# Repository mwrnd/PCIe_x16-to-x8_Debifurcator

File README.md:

# PCIe x16-to-x8 Debifurcator

Designed for use with the [Alveo U25](https://www.xilinx.com/products/boards-and-kits/alveo/u25.html) which has an x16 PCIe interface that is bifurcated to two x8 interfaces, one for the [SFC9250 X2 GbE Controller](https://www.xilinx.com/products/boards-and-kits/x2-series.html) and the other for the [XCZU19EG FPGA](https://www.xilinx.com/products/silicon-devices/soc/zynq-ultrascale-mpsoc.html#eg). This board connects the FPGA's PCIe x8 interface directly to a host system. The X2 GbE Controller is disconnected and ignored.

Only a straddle-mount PCIe x16 Connector is required, such as: [10025026-10103TLF](https://www.trustedparts.com/en/search/10025026-10103TLF), [10025026-10003TLF](https://www.trustedparts.com/en/search/10025026-10003TLF), or [10146027-A40010LF](https://www.trustedparts.com/en/search/10146027-A40010LF).

Related Projects: [alveo_u25_notes](https://github.com/mwrnd/alveo_u25_notes), [AlveoU25_JTAG_Adapter](https://github.com/mwrnd/AlveoU25_JTAG_Adapter), [ATX_Boot_Delay](https://github.com/mwrnd/ATX_Boot_Delay)

# Testing and Use Example

I have been able to [successfully test an XDMA design](https://github.com/mwrnd/alveo_u25_notes) using the debifurcator and an Alveo U25 in a system that does not support PCIe Bifurcation.

The XCZU19EG uses its ARM processor to configure the FPGA's Programmable Logic (PL) bitstream. It is difficult to get this to finish within the [PCIe Specification's 100ms time limit](https://pcisig.com/specifications/ecr_ecn_process?speclib=100+ms). Motherboard boot must be delayed to allow the FPGA to configure itself before PCIe devices are enumerated by the host system. This can be accomplished by toggling the POWER button, then pressing and holding the RESET button for a second before releasing it. Or, [connect a capacitor across the reset pins of an ATX motherboard's Front Panel Header](https://github.com/mwrnd/ATX_Boot_Delay):

# PCB Layout

All differential pairs are length-matched to within 1mm both inter-pair and intra-pair.

# Schematic

# Assembly

The PCIe Connector's Mounting Post needs to be snapped off with needle-nose pliers.

# PCB Layer Stackup

4-Layer PCB stackup taken from [JLCPCB](https://jlcpcb.com/capabilities/pcb-capabilities).

Differential Impedance parameters were calculated using the [DigiKey Online Calculator](https://www.digikey.com/en/resources/conversion-calculators/conversion-calculator-pcb-trace-impedance).

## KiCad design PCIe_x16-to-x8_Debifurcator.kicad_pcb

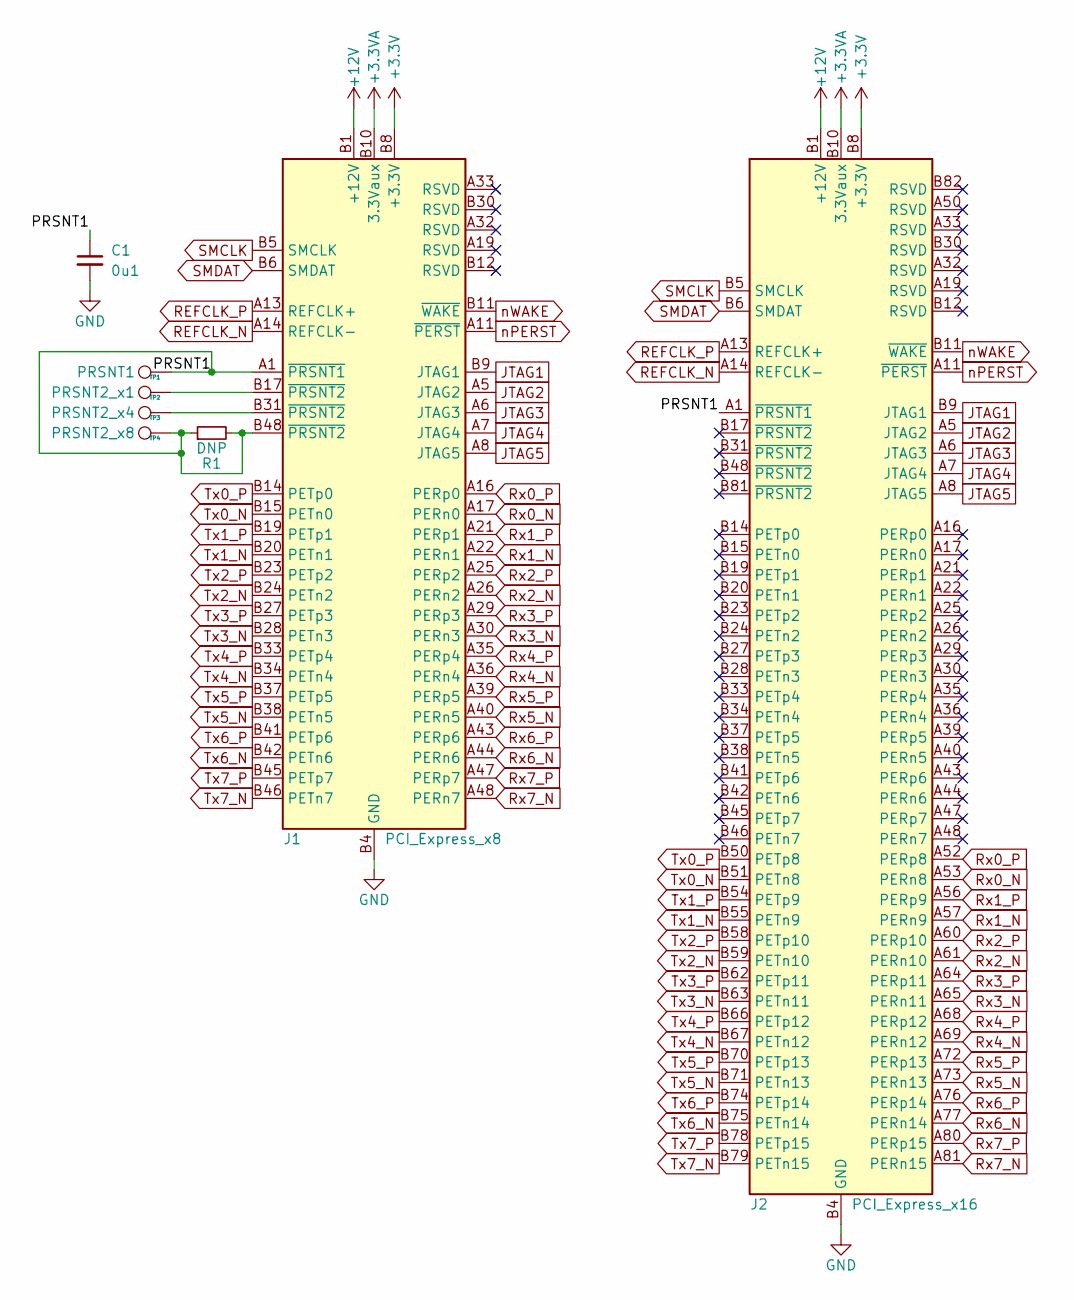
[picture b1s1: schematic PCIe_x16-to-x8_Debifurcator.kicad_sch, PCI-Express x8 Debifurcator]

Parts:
C1: 0u1; C_0603_1608Metric_Pad1.08x0.95mm_HandSolder
J1: PCI_Express_x8; BUS_PCIexpress_x8
J2: PCI_Express_x16; BUS_PCIexpress_x16
R1: DNP; R_0603_1608Metric
TP1: PRSNT1; PinHeader_1x01_P1.00mm_Vertical
TP2: PRSNT2_x1; PinHeader_1x01_P1.00mm_Vertical
TP3: PRSNT2_x4; PinHeader_1x01_P1.00mm_Vertical
TP4: PRSNT2_x8; PinHeader_1x01_P1.00mm_Vertical

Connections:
+3.3V: J1.A9 (+3.3V), J1.A10 (+3.3V), J1.B8 (+3.3V), J2.A9 (+3.3V), J2.A10 (+3.3V), J2.B8 (+3.3V)
+3.3VA: J1.B10 (3.3Vaux), J2.B10 (3.3Vaux)
+12V: J1.A2 (+12V), J1.A3 (+12V), J1.B1 (+12V), J1.B2 (+12V), J1.B3 (+12V), J2.A2 (+12V), J2.A3 (+12V), J2.B1 (+12V), J2.B2 (+12V), J2.B3 (+12V)
/PRSNT1: C1.1, J1.A1 (~PRSNT1), J1.B48 (~PRSNT2), J2.A1 (~PRSNT1), R1.1, R1.2, TP1.1, TP4.1
GND: C1.2, J1.A4 (GND), J1.A12 (GND), J1.A15 (GND), J1.A18 (GND), J1.A20 (GND), J1.A23 (GND), J1.A24 (GND), J1.A27 (GND), J1.A28 (GND), J1.A31 (GND), J1.A34 (GND), J1.A37 (GND), J1.A38 (GND), J1.A41 (GND), J1.A42 (GND), J1.A45 (GND), J1.A46 (GND), J1.A49 (GND), J1.B4 (GND), J1.B7 (GND), J1.B13 (GND), J1.B16 (GND), J1.B18 (GND), J1.B21 (GND), J1.B22 (GND), J1.B25 (GND), J1.B26 (GND), J1.B29 (GND), J1.B32 (GND), J1.B35 (GND), J1.B36 (GND), J1.B39 (GND), J1.B40 (GND), J1.B43 (GND), J1.B44 (GND), J1.B47 (GND), J1.B49 (GND), J2.A4 (GND), J2.A12 (GND), J2.A15 (GND), J2.A18 (GND), J2.A20 (GND), J2.A23 (GND), J2.A24 (GND), J2.A27 (GND), J2.A28 (GND), J2.A31 (GND), J2.A34 (GND), J2.A37 (GND), J2.A38 (GND), J2.A41 (GND), J2.A42 (GND), J2.A45 (GND), J2.A46 (GND), J2.A49 (GND), J2.A51 (GND), J2.A54 (GND), J2.A55 (GND), J2.A58 (GND), J2.A59 (GND), J2.A62 (GND), J2.A63 (GND), J2.A66 (GND), J2.A67 (GND), J2.A70 (GND), J2.A71 (GND), J2.A74 (GND), J2.A75 (GND), J2.A78 (GND), J2.A79 (GND), J2.A82 (GND), J2.B4 (GND), J2.B7 (GND), J2.B13 (GND), J2.B16 (GND), J2.B18 (GND), J2.B21 (GND), J2.B22 (GND), J2.B25 (GND), J2.B26 (GND), J2.B29 (GND), J2.B32 (GND), J2.B35 (GND), J2.B36 (GND), J2.B39 (GND), J2.B40 (GND), J2.B43 (GND), J2.B44 (GND), J2.B47 (GND), J2.B49 (GND), J2.B52 (GND), J2.B53 (GND), J2.B56 (GND), J2.B57 (GND), J2.B60 (GND), J2.B61 (GND), J2.B64 (GND), J2.B65 (GND), J2.B68 (GND), J2.B69 (GND), J2.B72 (GND), J2.B73 (GND), J2.B76 (GND), J2.B77 (GND), J2.B80 (GND)
JTAG1: J1.B9 (JTAG1), J2.B9 (JTAG1)
JTAG2: J1.A5 (JTAG2), J2.A5 (JTAG2)
JTAG3: J1.A6 (JTAG3), J2.A6 (JTAG3)
JTAG4: J1.A7 (JTAG4), J2.A7 (JTAG4)
JTAG5: J1.A8 (JTAG5), J2.A8 (JTAG5)
unnamed: J1.B17 (~PRSNT2), TP2.1
unnamed: J1.B31 (~PRSNT2), TP3.1
REFCLK_N: J1.A14 (REFCLK-), J2.A14 (REFCLK-)
REFCLK_P: J1.A13 (REFCLK+), J2.A13 (REFCLK+)
Rx0_N: J1.A17 (PERn0), J2.A53 (PERn8)
Rx0_P: J1.A16 (PERp0), J2.A52 (PERp8)
Rx1_N: J1.A22 (PERn1), J2.A57 (PERn9)
Rx1_P: J1.A21 (PERp1), J2.A56 (PERp9)
Rx2_N: J1.A26 (PERn2), J2.A61 (PERn10)
Rx2_P: J1.A25 (PERp2), J2.A60 (PERp10)
Rx3_N: J1.A30 (PERn3), J2.A65 (PERn11)
Rx3_P: J1.A29 (PERp3), J2.A64 (PERp11)
Rx4_N: J1.A36 (PERn4), J2.A69 (PERn12)
Rx4_P: J1.A35 (PERp4), J2.A68 (PERp12)
Rx5_N: J1.A40 (PERn5), J2.A73 (PERn13)
Rx5_P: J1.A39 (PERp5), J2.A72 (PERp13)
Rx6_N: J1.A44 (PERn6), J2.A77 (PERn14)
Rx6_P: J1.A43 (PERp6), J2.A76 (PERp14)
Rx7_N: J1.A48 (PERn7), J2.A81 (PERn15)
Rx7_P: J1.A47 (PERp7), J2.A80 (PERp15)
SMCLK: J1.B5 (SMCLK), J2.B5 (SMCLK)
SMDAT: J1.B6 (SMDAT), J2.B6 (SMDAT)
Tx0_N: J1.B15 (PETn0), J2.B51 (PETn8)
Tx0_P: J1.B14 (PETp0), J2.B50 (PETp8)
Tx1_N: J1.B20 (PETn1), J2.B55 (PETn9)
Tx1_P: J1.B19 (PETp1), J2.B54 (PETp9)
Tx2_N: J1.B24 (PETn2), J2.B59 (PETn10)
Tx2_P: J1.B23 (PETp2), J2.B58 (PETp10)
Tx3_N: J1.B28 (PETn3), J2.B63 (PETn11)
Tx3_P: J1.B27 (PETp3), J2.B62 (PETp11)
Tx4_N: J1.B34 (PETn4), J2.B67 (PETn12)
Tx4_P: J1.B33 (PETp4), J2.B66 (PETp12)
Tx5_N: J1.B38 (PETn5), J2.B71 (PETn13)
Tx5_P: J1.B37 (PETp5), J2.B70 (PETp13)
Tx6_N: J1.B42 (PETn6), J2.B75 (PETn14)
Tx6_P: J1.B41 (PETp6), J2.B74 (PETp14)
Tx7_N: J1.B46 (PETn7), J2.B79 (PETn15)
Tx7_P: J1.B45 (PETp7), J2.B78 (PETp15)
nPERST: J1.A11 (~PERST), J2.A11 (~PERST)
nWAKE: J1.B11 (~WAKE), J2.B11 (~WAKE)

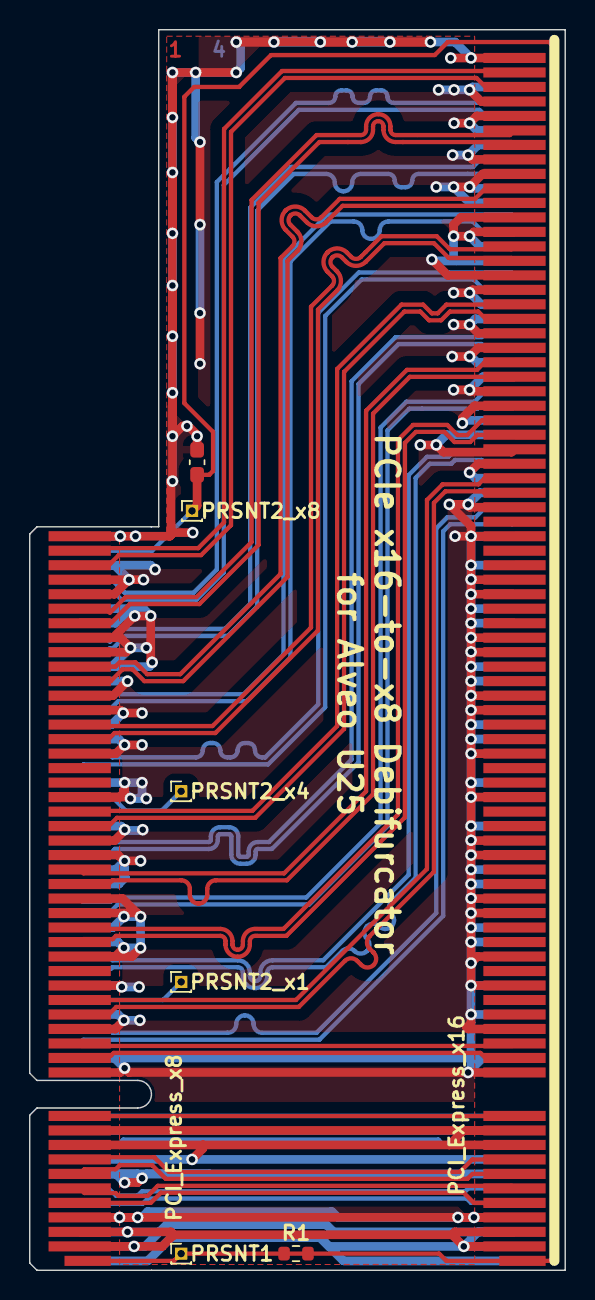
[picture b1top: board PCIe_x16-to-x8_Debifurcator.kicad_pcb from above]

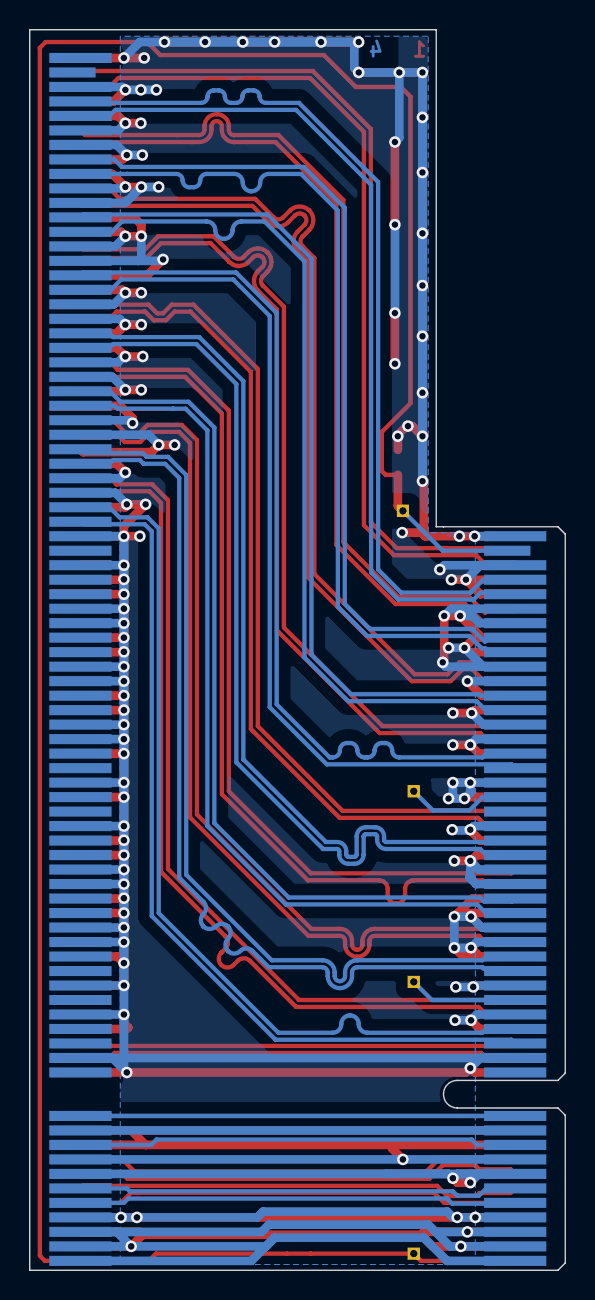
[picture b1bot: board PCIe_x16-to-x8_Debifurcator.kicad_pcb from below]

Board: 4 copper layers, 37.0 x 85.6 mm, 8 parts (2 on the bottom side), 50 nets.

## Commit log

2023-06-10 First Revision
2023-06-12 v0.1.1 PCB Layout Updated
2023-11-13 Ready for Release
2024-02-21 Updated Readme with Boot Delay
